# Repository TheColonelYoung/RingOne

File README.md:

# RingOne  
3D air mouse based on STM32  

Can be used for controlling CADs and every other manipulation in 3D space. Is based around STM32L452, IMU LSM6DSL (gyroscope and accelerometer) and Bluetooth low power module RN4871. Also contains battery management system for charging internal battery and also powering itself from this li-po battery (around 40 mah). Battery can be recharged via USB type C which can be also used for streaming data from accelerometer.  

Advanced USB capabilities are managed by STUSB1600 IC which communicate with host over CC lines. Button near bluettoth module serves as power up and also can be used to wake up device when is in power saving mode. For waking of device can be also used capability of accelerometer to detect taps. RGB LED diode is used to inform user about device status.  

During development, data can be saved to NOR Flash memory on board which is accessible via MCu CLI interface. Also connectors for SWD interface and debug UART are contained.  

## PCB  
 Front | Back |  
-------------------------|-------------------------|  
 |   

Note: black silk screen on back side of PCB should be also white, back color of silkscreen is probably result of some bug in Kicad rendering engine

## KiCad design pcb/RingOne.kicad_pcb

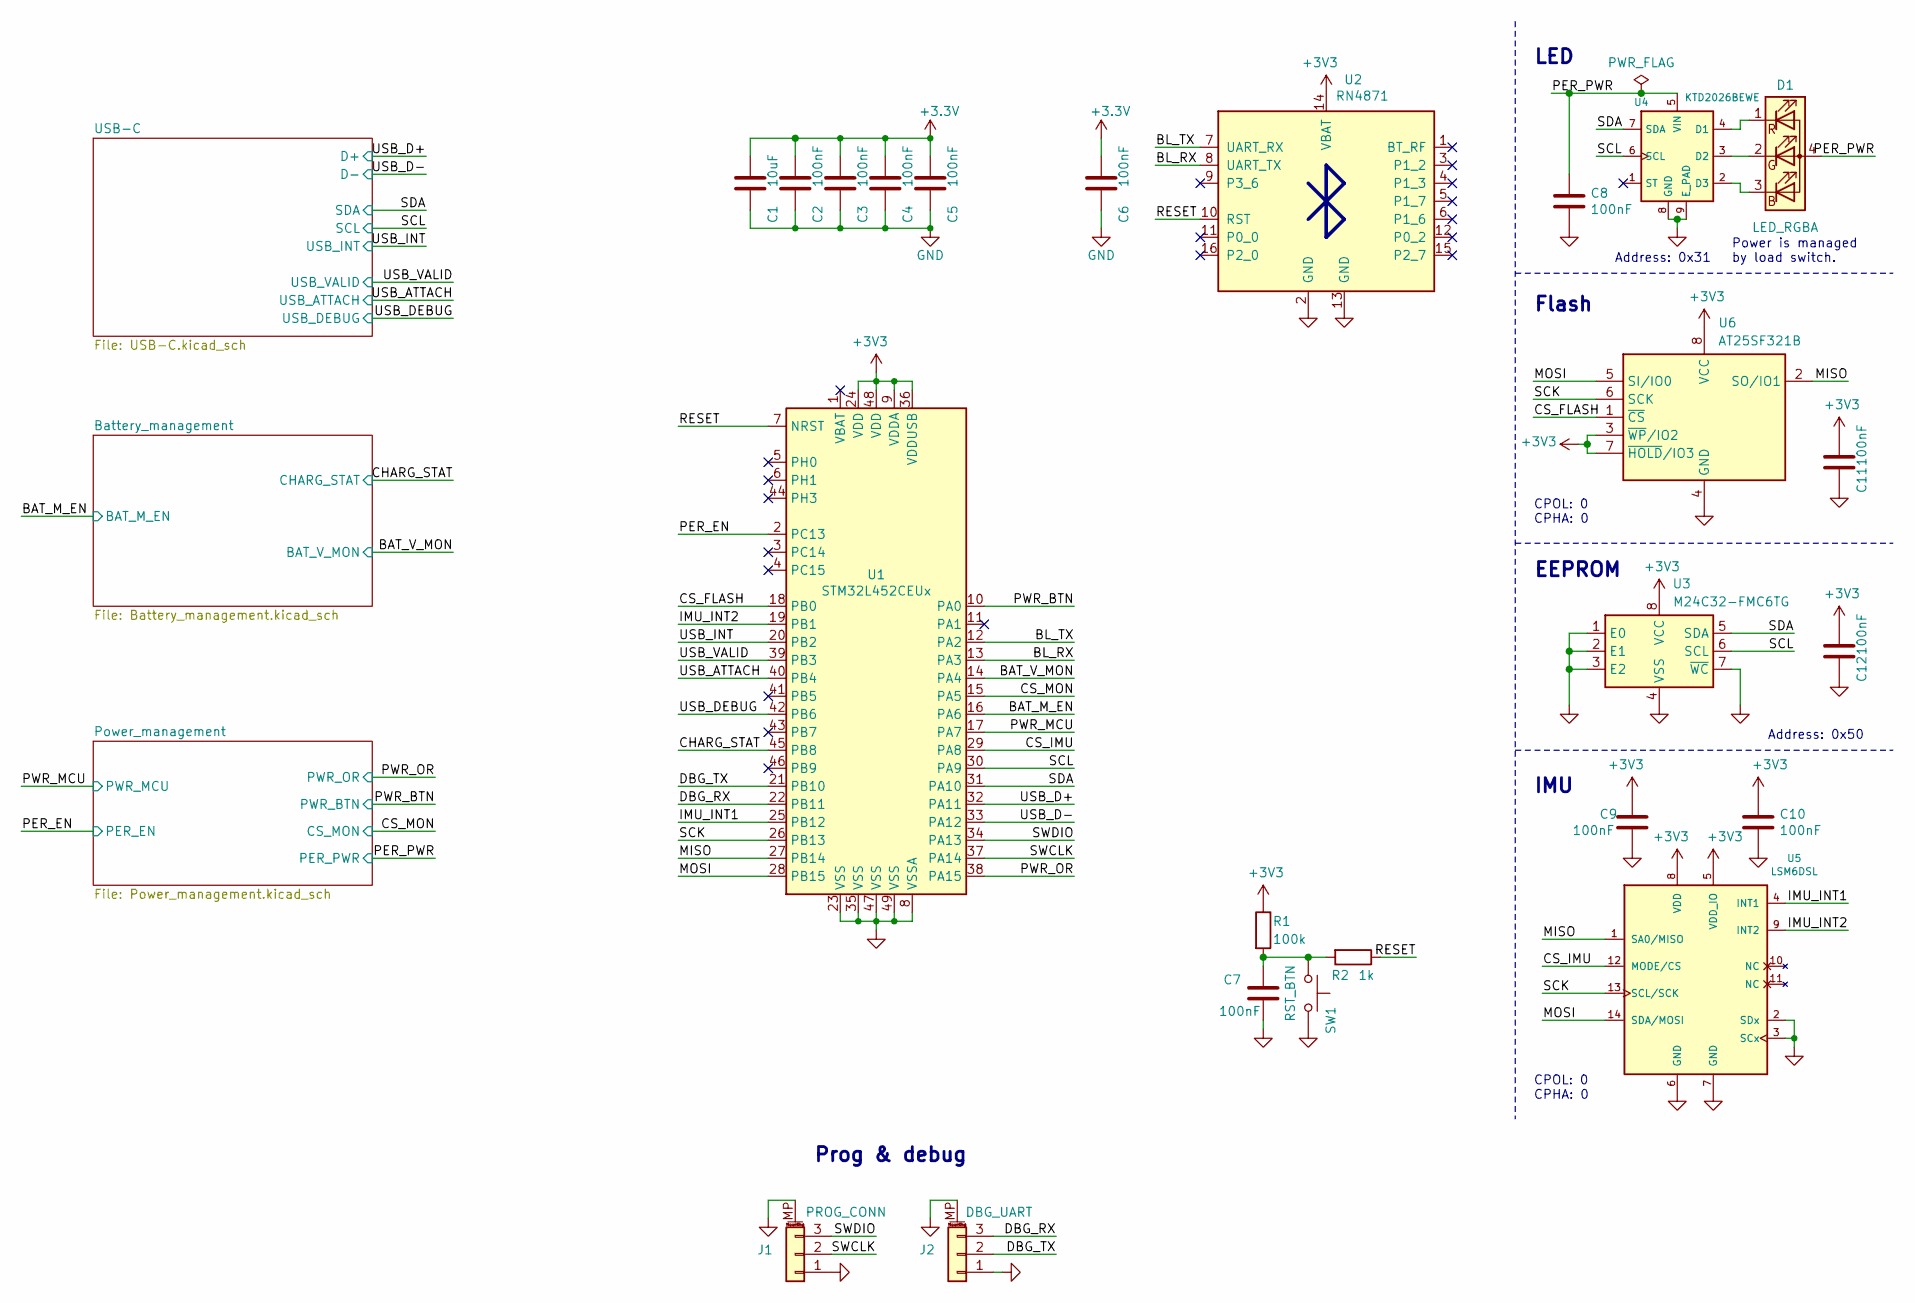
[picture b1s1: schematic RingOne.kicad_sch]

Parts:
C1: 10uF; C_0805_2012Metric
C2, C3, C4, C5, C6, C7, C8, C9, C10, C11, C12: 100nF; C_0603_1608Metric
D1: LED_RGBA; R_Array_Convex_2x0606
J1: PROG_CONN; Amphenol_10114830-11103LF_1x03_P1.25mm_Horizontal
J2: DBG_UART; Amphenol_10114830-11103LF_1x03_P1.25mm_Horizontal
R1: 100k; R_0603_1608Metric
R2: 1k; R_0603_1608Metric
SW1: RST_BTN; KMT031NGJLHS
U1: STM32L452CEUx; QFN-48-1EP_7x7mm_P0.5mm_EP5.6x5.6mm
U2: RN4871; Microchip_RN4871
U3: M24C32-FMC6TG; DFN-8-1EP_3x2mm_P0.5mm_EP1.3x1.5mm
U4: KTD2026BEWE; UTDFN-8-1EP_1.5x1.5mm_P0.4mm_EP0.8x1.45mm
U5: LSM6DSL; LGA-14_3x2.5mm_P0.5mm_LayoutBorder3x4y
U6: AT25SF321B; DFN-8-1EP_6x5mm_P1.27mm_EP4x4mm

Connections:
/BAT_M_EN: U1.16 (PA6); also elsewhere on the board
/BAT_V_MON: U1.14 (PA4); also elsewhere on the board
/BL_RX: U1.13 (PA3), U2.8 (UART_TX)
/BL_TX: U1.12 (PA2), U2.7 (UART_RX)
/CHARG_STAT: U1.45 (PB8); also elsewhere on the board
/CS_FLASH: U1.18 (PB0), U6.1 (~CS)
/CS_IMU: U1.29 (PA8), U5.12 (MODE/CS)
/CS_MON: U1.15 (PA5); also elsewhere on the board
/DBG_RX: J2.3, U1.22 (PB11)
/DBG_TX: J2.2, U1.21 (PB10)
/IMU_INT1: U1.25 (PB12), U5.4 (INT1)
/IMU_INT2: U1.19 (PB1), U5.9 (INT2)
/MISO: U1.27 (PB14), U5.1 (SA0/MISO), U6.2 (SO/IO1)
/MOSI: U1.28 (PB15), U5.14 (SDA/MOSI), U6.5 (SI/IO0)
/PER_EN: U1.2 (PC13); also elsewhere on the board
/PER_PWR: C8.1, D1.4 (A), U4.5 (VIN); also elsewhere on the board
/PWR_BTN: U1.10 (PA0); also elsewhere on the board
/PWR_MCU: U1.17 (PA7); also elsewhere on the board
/PWR_OR: U1.38 (PA15); also elsewhere on the board
/RESET: R2.1, U1.7 (NRST), U2.10 (RST)
/SCK: U1.26 (PB13), U5.13 (SCL/SCK), U6.6 (SCK)
/SCL: U1.30 (PA9), U3.6 (SCL), U4.6 (SCL); also elsewhere on the board
/SDA: U1.31 (PA10), U3.5 (SDA), U4.7 (SDA); also elsewhere on the board
/SWCLK: J1.2, U1.37 (PA14)
/SWDIO: J1.3, U1.34 (PA13)
/USB_ATTACH: U1.40 (PB4); also elsewhere on the board
/USB_D+: U1.32 (PA11); also elsewhere on the board
/USB_D-: U1.33 (PA12); also elsewhere on the board
/USB_DEBUG: U1.42 (PB6); also elsewhere on the board
/USB_INT: U1.20 (PB2); also elsewhere on the board
/USB_VALID: U1.39 (PB3); also elsewhere on the board
GND: C1.2, C2.2, C3.2, C4.2, C5.2, C6.2, C7.2, C8.2, C9.2, C10.2, C11.2, C12.2, J1.1, J1.MP (MountPin), J2.1, J2.MP (MountPin), SW1.2, U1.8 (VSSA), U1.23 (VSS), U1.35 (VSS), U1.47 (VSS), U1.49 (VSS), U2.2 (GND), U2.13 (GND), U3.1 (E0), U3.2 (E1), U3.3 (E2), U3.4 (VSS), U3.7 (~WC), U4.8 (GND), U4.9 (E_PAD), U5.2 (SDx), U5.3 (SCx), U5.6 (GND), U5.7 (GND), U6.4 (GND); also elsewhere on the board
unnamed: C7.1, R1.2, R2.2, SW1.1
unnamed: D1.1 (RK), U4.4 (D1)
unnamed: D1.2 (GK), U4.3 (D2)
unnamed: D1.3 (BK), U4.2 (D3)
no_connect_71: U1.1 (VBAT)
no_connect_72: U1.11 (PA1)
no_connect_73: U1.3 (PC14)
no_connect_74: U1.4 (PC15)
no_connect_75: U1.41 (PB5)
no_connect_76: U1.43 (PB7)
no_connect_77: U1.44 (PH3)
no_connect_78: U1.46 (PB9)
no_connect_79: U1.5 (PH0)
no_connect_80: U1.6 (PH1)
no_connect_81: U2.1 (BT_RF)
no_connect_82: U2.11 (P0_0)
no_connect_83: U2.12 (P0_2)
no_connect_84: U2.15 (P2_7)
no_connect_85: U2.16 (P2_0)
no_connect_86: U2.3 (P1_2)
no_connect_87: U2.4 (P1_3)
no_connect_88: U2.5 (P1_7)
no_connect_89: U2.6 (P1_6)
no_connect_90: U2.9 (P3_6)
no_connect_91: U4.1 (ST)
no_connect_95: U5.10 (NC)
no_connect_96: U5.11 (NC)

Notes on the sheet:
IMU
LED
CPOL: 0 CPHA: 0
Address: 0x50
EEPROM
Address: 0x31
Power is managed by load switch.
Flash
Prog & debug

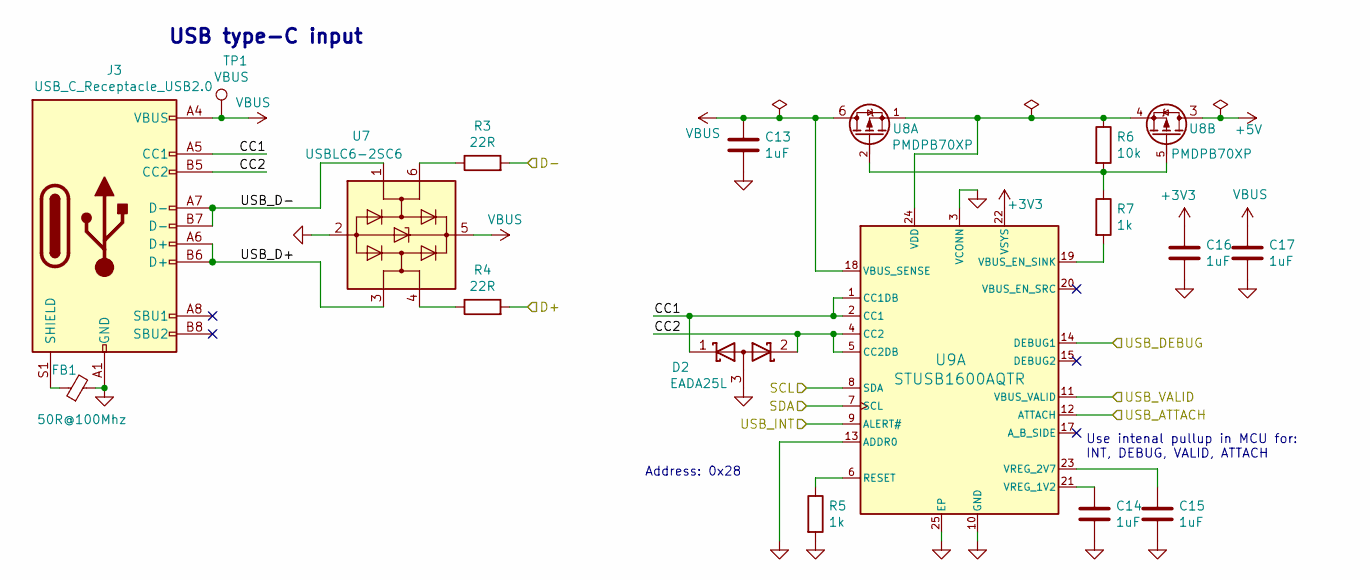
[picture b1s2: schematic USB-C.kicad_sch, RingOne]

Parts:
C13, C14, C15, C16, C17: 1uF; C_0603_1608Metric
D2: EADA25L; SOT-23
FB1: 50R@100Mhz; L_1206_3216Metric
J3: USB_C_Receptacle_USB2.0; USB_C_Receptacle_HRO_TYPE-C-31-M-12
R3, R4: 22R; R_0603_1608Metric
R5, R7: 1k; R_0603_1608Metric
R6: 10k; R_0603_1608Metric
TP1: VBUS; TestPoint_Pad_D0.5mm
U7: USBLC6-2SC6; SOT-23-6
U8: PMDPB70XP; UDFN-6-2EP_2x2mm_P0.65mm_EP1x0.7mm
U9: STUSB1600AQTR; QFN-24-1EP_4x4mm_P0.5mm_EP2.7x2.7mm

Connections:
+5V: U8.3, U8.8; also elsewhere on the board
/SCL: U9.8 (SDA); also elsewhere on the board
/SDA: U9.7 (SCL); also elsewhere on the board
/USB-C/CC1: D2.1 (K), J3.A5 (CC1), U9.1 (CC1DB), U9.2 (CC1)
/USB-C/CC2: D2.2 (K), J3.B5 (CC2), U9.4 (CC2), U9.5 (CC2DB)
/USB-C/USB_D+: J3.A6 (D+), J3.B6 (D+), U7.3 (I/O2)
/USB-C/USB_D-: J3.A7 (D-), J3.B7 (D-), U7.1 (I/O1)
/USB_ATTACH: U9.12 (ATTACH); also elsewhere on the board
/USB_D+: R4.2; also elsewhere on the board
/USB_D-: R3.2; also elsewhere on the board
/USB_DEBUG: U9.14 (DEBUG1); also elsewhere on the board
/USB_INT: U9.9 (ALERT#); also elsewhere on the board
/USB_VALID: U9.11 (VBUS_VALID); also elsewhere on the board
GND: C13.2, C14.2, C15.2, C16.2, C17.2, D2.3 (A), FB1.2, J3.A1 (GND), J3.A12 (GND), J3.B1 (GND), J3.B12 (GND), R5.2, U7.2 (GND), U9.3 (VCONN), U9.10 (GND), U9.13 (ADDR0), U9.25 (EP); also elsewhere on the board
unnamed: C14.1, U9.21 (VREG_1V2)
unnamed: C15.1, U9.23 (VREG_2V7)
unnamed: FB1.1, J3.S1 (SHIELD)
unnamed: R3.1, U7.6 (I/O1)
unnamed: R4.1, U7.4 (I/O2)
unnamed: R5.1, U9.6 (RESET)
unnamed: R6.1, U8.1, U8.4, U9.24 (VDD)
unnamed: R6.2, R7.1, U8.2, U8.5
unnamed: R7.2, U9.19 (VBUS_EN_SINK)
VBUS: C13.1, C17.1, J3.A4 (VBUS), J3.A9 (VBUS), J3.B4 (VBUS), J3.B9 (VBUS), TP1.1, U7.5 (VBUS), U8.6, U8.7, U9.18 (VBUS_SENSE)
no_connect_69: J3.A8 (SBU1)
no_connect_70: J3.B8 (SBU2)
no_connect_92: U9.15 (DEBUG2)
no_connect_93: U9.17 (A_B_SIDE)
no_connect_94: U9.20 (VBUS_EN_SRC)

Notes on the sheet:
Address: 0x28
USB type-C input
Use intenal pullup in MCU for: INT, DEBUG, VALID, ATTACH

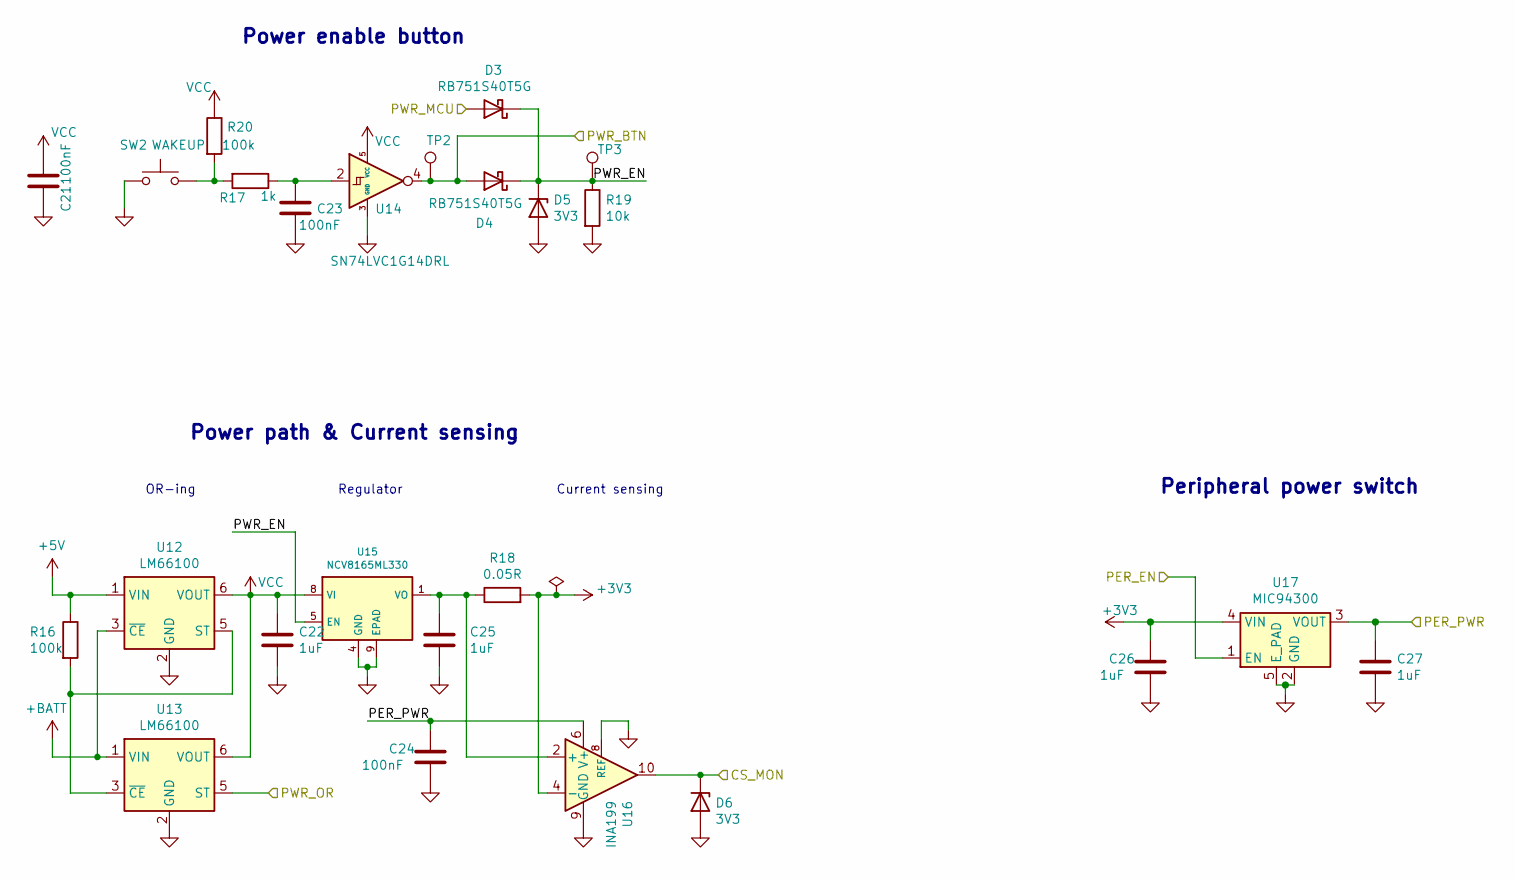
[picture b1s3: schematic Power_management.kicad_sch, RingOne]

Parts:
C21, C23, C24: 100nF; C_0603_1608Metric
C22, C25, C26, C27: 1uF; C_0603_1608Metric
D3, D4: RB751S40T5G; D_SOD-523
D5, D6: 3V3; D_SOD-523
R16, R20: 100k; R_0603_1608Metric
R17: 1k; R_0603_1608Metric
R18: 0.05R; R_0603_1608Metric
R19: 10k; R_0603_1608Metric
SW2: WAKEUP; EVQ-P7J01P
TP2, TP3: TestPoint; TestPoint_Pad_D0.5mm
U12, U13: LM66100; SOT-363_SC-70-6
U14: SN74LVC1G14DRL; SOT-553
U15: NCV8165ML330; DFN-8-1EP_3x3mm_P0.65mm_EP1.55x2.4mm
U16: INA199; UQFN-10_1.4x1.8mm_P0.4mm
U17: MIC94300; MLF-4_1.2x1.6mm_P0.5_1EP_0.85x0.5mm

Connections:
+5V: R16.1, U12.1 (VIN); also elsewhere on the board
+BATT: U12.3 (~CE), U13.1 (VIN); also elsewhere on the board
/CS_MON: D6.1 (K), U16.10; also elsewhere on the board
/PER_EN: U17.1 (EN); also elsewhere on the board
/PER_PWR: C24.1, C27.1, U16.6 (V+), U17.3 (VOUT); also elsewhere on the board
/PWR_BTN: D4.2 (A), TP2.1, U14.4; also elsewhere on the board
/PWR_MCU: D3.2 (A); also elsewhere on the board
/PWR_OR: U13.5 (ST); also elsewhere on the board
/Power_management/PWR_EN: D3.1 (K), D4.1 (K), D5.1 (K), R19.1, TP3.1, U15.5 (EN)
GND: C21.2, C22.2, C23.2, C24.2, C25.2, C26.2, C27.2, D5.2 (A), D6.2 (A), R19.2, SW2.1, U12.2 (GND), U13.2 (GND), U14.3 (GND), U15.4 (GND), U15.9 (EPAD), U16.8 (REF), U16.9 (GND), U17.2 (GND), U17.5 (E_PAD); also elsewhere on the board
unnamed: C23.1, R17.1, U14.2
unnamed: C25.1, R18.1, U15.1 (VO), U16.2 (+), U16.3 (+)
unnamed: R16.2, U12.5 (ST), U13.3 (~CE)
unnamed: R17.2, R20.2, SW2.2
VCC: C21.1, C22.1, R20.1, U12.6 (VOUT), U13.6 (VOUT), U14.5 (VCC), U15.8 (VI)
no_connect_98: U14.1 (NC)

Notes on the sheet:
Regulator
Power path & Current sensing
Current sensing
Power enable button
Peripheral power switch
OR-ing

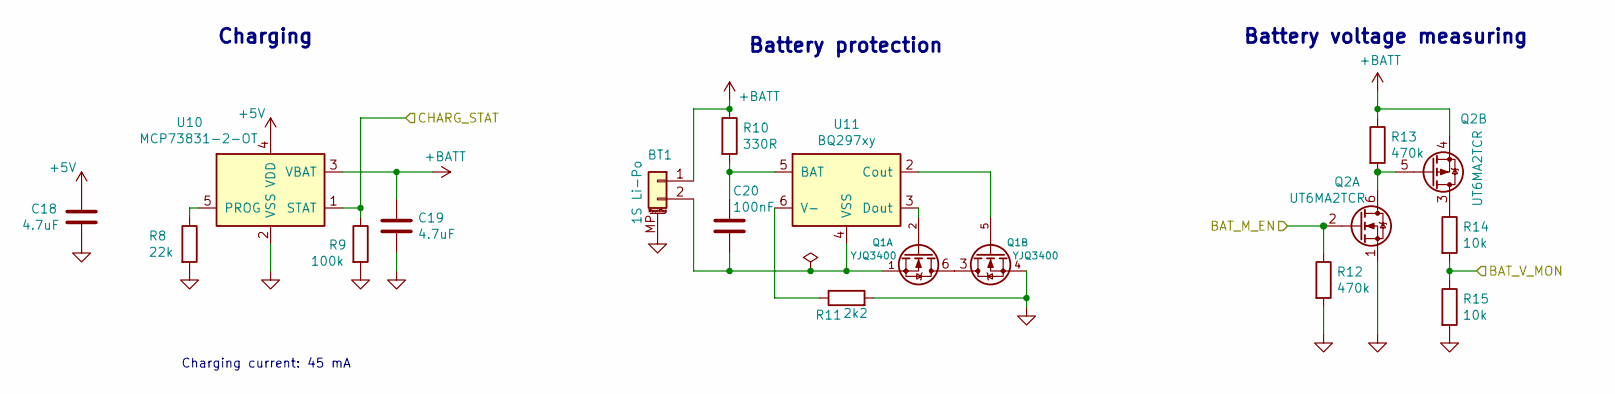
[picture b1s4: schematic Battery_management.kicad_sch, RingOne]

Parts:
BT1: 1S Li-Po; Amphenol_10114830-11102LF_1x02_P1.25mm_Horizontal
C18, C19: 4.7uF; C_0603_1608Metric
C20: 100nF; C_0603_1608Metric
Q1: YJQ3400; UDFN-6-2EP_2x2mm_P0.65mm_EP1x0.7mm
Q2: UT6MA2TCR; UDFN-6-2EP_2x2mm_P0.65mm_EP1x0.7mm
R8: 22k; R_0603_1608Metric
R9: 100k; R_0603_1608Metric
R10: 330R; R_0603_1608Metric
R11: 2k2; R_0603_1608Metric
R12, R13: 470k; R_0603_1608Metric
R14, R15: 10k; R_0603_1608Metric
U10: MCP73831-2-OT; SOT-23-5
U11: BQ297xy; WSON-6_1.5x1.5mm_P0.5mm

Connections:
+5V: C18.1, U10.4 (VDD); also elsewhere on the board
+BATT: BT1.1, C19.1, Q2.4 (SP), Q2.8 (SP), R10.1, R13.1, U10.3 (VBAT); also elsewhere on the board
/BAT_M_EN: Q2.2 (GN), R12.1; also elsewhere on the board
/BAT_V_MON: R14.2, R15.1; also elsewhere on the board
/CHARG_STAT: R9.1, U10.1 (STAT); also elsewhere on the board
GND: BT1.MP (MountPin), C18.2, C19.2, Q1.4 (S2), Q2.1 (SN), R8.2, R9.2, R11.2, R12.2, R15.2, U10.2 (VSS); also elsewhere on the board
unnamed: C20.1, R10.2, U11.5 (BAT)
unnamed: BT1.2, C20.2, Q1.1 (S), U11.4 (VSS)
unnamed: Q1.2 (G1), U11.3 (Dout)
unnamed: Q1.3 (D2), Q1.6 (D2), Q1.7 (D2), Q1.8 (D2)
unnamed: Q1.5 (G2), U11.2 (Cout)
unnamed: Q2.3 (DP), R14.1
unnamed: Q2.5 (GP), Q2.6 (DN), Q2.7 (DN), R13.2
unnamed: R8.1, U10.5 (PROG)
unnamed: R11.1, U11.6 (V-)
no_connect_97: U11.1 (NC)

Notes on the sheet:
Charging
Charging current: 45 mA
Battery voltage measuring
Battery protection

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
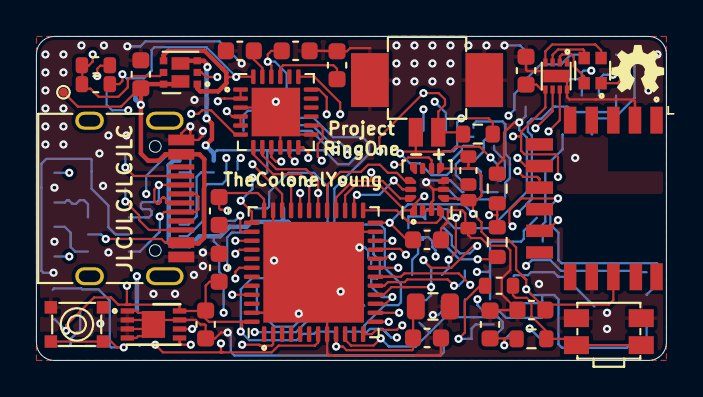
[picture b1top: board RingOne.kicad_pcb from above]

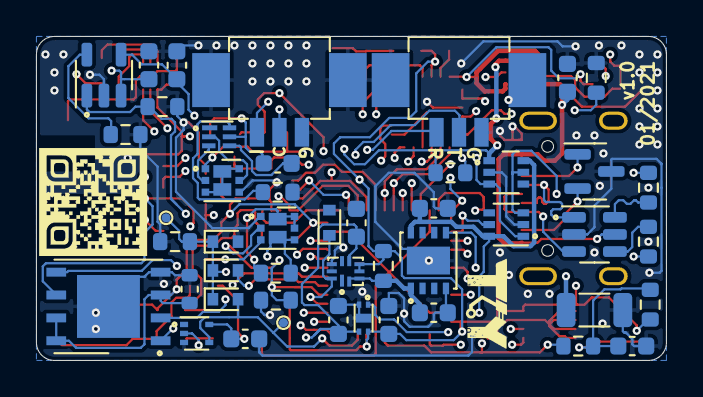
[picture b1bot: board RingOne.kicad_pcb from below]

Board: 4 copper layers, 35.0 x 18.0 mm, 82 parts (47 on the bottom side), 68 nets.

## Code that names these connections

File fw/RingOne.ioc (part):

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Mcu.Name=STM32L452C(C-E)Ux
Mcu.Package=UFQFPN48
Mcu.UserName=STM32L452CEUx
PA0.GPIOParameters=GPIO_Label
PA0.GPIO_Label=PWR_BTN
PA0.Mode=SYS_WakeUp0
PA0.Signal=SYS_WKUP1
PA10.Mode=I2C
PA10.Signal=I2C1_SDA
PA11.Mode=Device
PA11.Signal=USB_DM
PA12.Mode=Device
PA12.Signal=USB_DP
PA13\ (JTMS/SWDIO).GPIOParameters=GPIO_Label
PA13\ (JTMS/SWDIO).GPIO_Label=SWDIO
PA13\ (JTMS/SWDIO).Mode=Serial_Wire
PA13\ (JTMS/SWDIO).Signal=SYS_JTMS-SWDIO
PA14\ (JTCK/SWCLK).GPIOParameters=GPIO_Label
PA14\ (JTCK/SWCLK).GPIO_Label=SWCLK
PA14\ (JTCK/SWCLK).Mode=Serial_Wire
PA14\ (JTCK/SWCLK).Signal=SYS_JTCK-SWCLK
PA15\ (JTDI).GPIOParameters=GPIO_Label
PA15\ (JTDI).GPIO_Label=PWR_OR
PA15\ (JTDI).Signal=GPIO_Output
PA2.GPIOParameters=GPIO_Label
PA2.GPIO_Label=BL_TX_LP
PA2.Mode=Asynchronous
PA2.Signal=LPUART1_TX
PA3.GPIOParameters=GPIO_Label
PA3.GPIO_Label=BL_RX_LP
PA3.Mode=Asynchronous
PA3.Signal=LPUART1_RX
PA4.GPIOParameters=GPIO_Label
PA4.GPIO_Label=BAT_V_MON
PA4.Signal=ADCx_IN9
PA5.GPIOParameters=GPIO_Label
PA5.GPIO_Label=CS_MON
PA5.Signal=ADCx_IN10
PA6.GPIOParameters=GPIO_Label
PA6.GPIO_Label=BAT_M_EN
PA6.Signal=GPIO_Output
PA7.GPIOParameters=GPIO_Label
PA7.GPIO_Label=PWR_MCU
PA7.Signal=GPIO_Output
PA8.GPIOParameters=GPIO_Label
PA8.GPIO_Label=CS_IMU
PA8.Signal=GPIO_Output
PA9.Mode=I2C
PA9.Signal=I2C1_SCL
PB0.GPIOParameters=GPIO_Label
PB0.GPIO_Label=CS_FLASH
PB0.Signal=GPXTI0
PB1.GPIOParameters=GPIO_Label
PB1.GPIO_Label=IMU_INT2
PB1.Signal=GPXTI1
PB10.GPIOParameters=GPIO_Label
PB10.GPIO_Label=DBG_TX
PB10.Mode=Asynchronous
PB10.Signal=USART3_TX
PB11.GPIOParameters=GPIO_Label
PB11.GPIO_Label=DBG_RX
PB11.Mode=Asynchronous
PB11.Signal=USART3_RX
PB12.GPIOParameters=GPIO_Label
PB12.GPIO_Label=IMU_INT1
PB12.Signal=GPIO_Output
PB13.Mode=Full_Duplex_Master
PB13.Signal=SPI2_SCK
PB14.Mode=Full_Duplex_Master
PB14.Signal=SPI2_MISO
PB15.Mode=Full_Duplex_Master
PB15.Signal=SPI2_MOSI
PB2.GPIOParameters=GPIO_Label
PB2.GPIO_Label=USB_INT
PB2.Signal=GPXTI2
PB3\ (JTDO/TRACESWO).GPIOParameters=GPIO_Label
PB3\ (JTDO/TRACESWO).GPIO_Label=USB_VALID
PB3\ (JTDO/TRACESWO).Signal=GPXTI3
PB4\ (NJTRST).GPIOParameters=GPIO_Label
PB4\ (NJTRST).GPIO_Label=USB_ATTACH
PB4\ (NJTRST).Signal=GPXTI4
PB6.GPIOParameters=GPIO_Label
PB6.GPIO_Label=USB_DEBUG
PB6.Signal=GPIO_Input
PB8.GPIOParameters=GPIO_Label
PB8.GPIO_Label=CHARG_STAT
PB8.Signal=GPIO_Input
PC13.GPIOParameters=GPIO_Label
PC13.GPIO_Label=PER_EN
PC13.Signal=GPIO_Output
RCC.HSE_VALUE=8000000
RCC.SYSCLKFreq_VALUE=80000000
RCC.SYSCLKSource=RCC_SYSCLKSOURCE_PLLCLK
board=custom

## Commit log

2021-01-18 KiCAD project initialization
2021-01-20 KiCAD: update library paths
2021-01-20 Schema: initial placing of components
2021-01-21 Schema: add power path control, input button and bluetooth module
2021-01-23 Schema: finalization of schematic, break main page into hierarchical
2021-01-23 PCB: routing of all components
2021-01-23 CubeMX initialization, MCU pin function assignment
2021-01-25 PCB & Schema: update page layout
2021-01-26 Notes: update readme and add images
2021-01-28 Schema & PCB: add pull up to wakeup button
2021-02-01 PCB: add connection of connector mounting point to ground
2021-02-01 FW: update path to CubeMX config
2021-05-21 Errata: add initial errata
2021-05-21 FW: generate MCU project from CubeMX
2021-06-09 project: remove build folder from git
2021-06-09 project: update cubeMX and compilation settings
2021-06-09 project: add I2C scanner app and peripheral powerup
2022-06-13 FW: add testing of connection with LED driver, IMU and Bluetooth module
2022-06-13 Schema & PCB: Update page layout, add notes about SPI modes and I2C addresses
2022-06-13 Errata: add section about STUSB1600 and LED PCB layout
